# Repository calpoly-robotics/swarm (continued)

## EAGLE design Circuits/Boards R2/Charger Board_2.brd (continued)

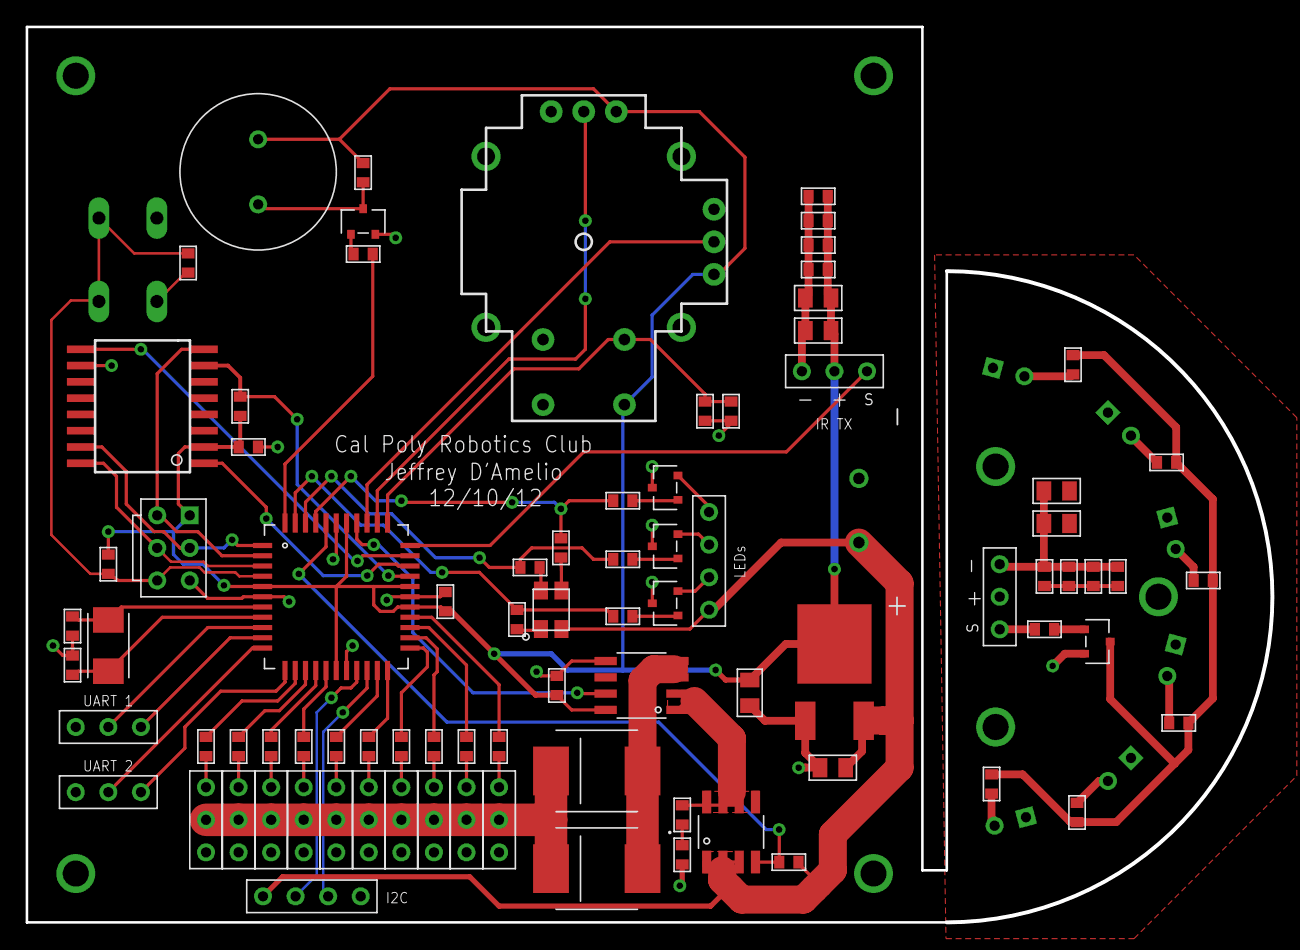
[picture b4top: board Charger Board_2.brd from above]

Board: 2 copper layers, 97.2 x 69.8 mm, 100 parts (1 on the bottom side), 74 nets.

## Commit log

2012-05-16 test
2012-05-16 putting real files in the SVN!
2012-05-16 changed main.c
2012-05-16 added serial library
2012-05-16 minor change
2012-05-17 Cleaned up the serial code a bit.
2012-05-17 renamed uartReady() to uartDataAvailable()
2012-05-17 solid modeled motor and wheels(s)
2012-05-18 uploaded google doc docs
2012-05-22 somebody messed up the svn!
2012-05-23 some ir message code
2012-05-23 ir files
2012-05-23 ir update
2012-05-23 Cleaned up some header files.
2012-05-23 Added parity code.
2012-05-23 better parity
2012-05-23 cleaned up code
2012-05-23 updated a lot of solid modeling parts, not yet complete
2012-05-26 Redid IR stuff to use new struct.
2012-05-26 Added interrupts for transmitting and added start pulse of 3.5 counts to messages.
2012-05-29 Added datasheet.
2012-05-29 Finished Charger?
2012-05-30 updated the wheels, acrylic base, and output a couple images. To laser cut the wheels, it would be best to consider the laser's thickness so that the key is accurate
2012-07-17 massive eagle update
2012-07-18 updates to swarm board circuit
2012-07-19 more work
2012-07-22 added datasheet for mcp73832
2012-07-22 renamed swarm bot overall to swarm board
2012-07-22 added Charger Board.sch
2012-07-22 updated charger schematic, and added swarm board board file
2012-07-22 updated libraries with new datasheets
2012-07-22 Large updates to the charger board
2012-07-24 updates to both boards and libraries. Added hall effect sensors to charger board
2012-08-01 updated libraries and charger board
2012-08-02 updates to both boards
2012-08-02 Started Routing, kill me now
2012-08-11 Finished routing
2012-08-15 changed charge circuit to incorporate mcp73833 and p-fet/diode for ppm
2012-08-16 started routing new charger
2012-08-27 Updated README so it would be more complete.
2012-09-24 basic calculations for the clock in clockCalculations.xlsx
2012-09-24 updated clockCalculations.xlsx to show ticks/second
2012-10-01 updated datasheet
2012-10-01 Updated messages.h to use an enum
2012-10-01 Added test code. Updated main code makefile.
2012-10-01 Added back .c files.
2012-10-01 fixed incorrect vector name
2012-10-01 fixed globals.h
2012-10-05 Instructions for using the laser cutter
2012-10-08 Moved solidworks files into their own folder
2012-10-08 moved more svn stuff
2012-10-13 This code makes the buzzer make noise.
2012-10-14 updated swarm board with R2 and started charger board changes
2012-10-16 Added message format document (and picture).
2012-10-16 fixed syntax
2012-10-16 updated message format
2012-10-17 updated R2 board
2012-10-20 changed spacing on ISP header
2012-10-20 Motors!
2012-10-20 OCR0A, not OCR0B
2012-10-20 reorganizing!
2012-10-20 It drives.
2012-10-20 Added red/green led code
2012-10-20 added u32
2012-10-20 Started work on multitasking
2012-10-20 Clock
2012-10-22 Should work, needs testing.
2012-10-22 Added functions to libraries
2012-10-22 added short range IR code
2012-10-22 We can count on the clock working now.
2012-10-24 modular
2012-10-24 lots of message sending and receiving code
2012-10-24 added tasks
2012-10-24 Merged Jeffrey's task code into the main code folder.
2012-10-24 organized main code
2012-10-25 Clock worked, it's better now too. Don't try to store 32 bit values in 8 bit variables :P
2012-10-25 Clock is more modular now.
2012-11-05 This is a test
2012-11-05 testing svn
2012-11-16 saving charger changes
2012-11-17 combined drivers
2012-11-26 completed schematic for the charger board
2012-11-26 more board updates
2012-11-26 added sparkfun drc
2012-11-27 started adding rgb edge lighting hardware
2012-12-03 fixed led on swarm board
2012-12-09 added boms for run 2
2012-12-09 slight updates to part values to account for availibility
2012-12-10 added gerbers for production
2013-02-15 reorganized code, added some new base code
2013-10-14 Removed drivers folder
2013-10-14 Removed files
2013-10-14 Reorganized
2013-10-14 Reorganized. Conversion from svn is complete. I think.
2013-11-01 Added base files
2013-11-01 Removed binary files
2013-11-02 Added .gitignore
2013-11-02 Clock init stuff
2013-11-02 Added basic code for the motors. Need to figure out what the pins mean...
2013-11-02 Minor work on motor init
2013-11-03 On branch master Changes to be committed: (use "git reset HEAD <file>..." to unstage)
    modified: Robot/Makefile
    modified: Robot/main.c
    modified: Robot/main.elf
    modified: Robot/main.hex
    modified: Robot/swarm.conf
2013-11-14 Added a bunch of drivers
2013-11-15 Did some serial stuff
2013-11-15 More work done on serial
2013-11-16 did some stuff...
2013-11-16 Should now be able to add tasks with an expanding array
2013-11-16 I think tasks work now...
2013-11-16 Well, tasks should be done...
2013-11-16 added dummy tasks for all the things
2013-11-16 Added all dummy tasks and MULTITASKING WORKS!!!
2013-11-16 Code mostly done for IR. Just need recieve manager...
2013-11-16 IR is done. I think.. Need to test.
2013-11-16 Renamed some stuff.
2013-11-16 Added header for TWI(I2C)
2013-11-16 Added eeprom and twi(i2c) templates
2013-11-16 Working on TWI(I2C) protocol...
2013-11-17 More work on TWI
2013-11-17 Stuff...
2013-11-17 Filled out README.md with more notes
2013-11-17 Much work done on TWI
2013-11-18 changed header defs slightly. can read eeprom log
2013-11-18 More improvements on eeprom stuff. i think it's "done"
2013-11-18 i think transmittion is done
2013-11-18 Added gitignore
2013-11-18 Auto retransmit of messages and ignore our messages that got retransmitted
2013-11-18 Working on pins.h
2013-11-18 I think pins.h is done?
2013-11-18 Fixed a typo and wrote down some todos
2013-11-19 Part of buzzer code done. The annoying math part
2013-11-19 Added some buzzer stuff
2013-11-19 Too hard to test without actual hardware...:
2013-11-21 stuff
2013-11-23 Led stuff done. I think
2013-12-12 Began work on battery monitoring task. Fixed adc code. SERIAL!!!
2013-12-12 Add base code
2013-12-12 Minor changes to main and battery
2013-12-12 warning level mostly done
2013-12-13 Low power modes done coding. Testing to ensue
2013-12-13 Fixed possible uart buffer problems
2013-12-13 Minor changes to serial
2013-12-13 Goofed with the merge
2013-12-13 main now echos anything sent
2014-01-26 such change.
2014-01-30 Added some shit right there. Yup
2014-01-31 updated project file
2014-01-31 fixed project file
2014-01-31 Updated the uart code
2014-02-01 fixed some multitasking stuff
2014-02-02 much pain...
2014-02-02 Forgot these files
2014-02-07 IR is closer to working....
2014-02-07 asdf
2014-02-27 Working on ir test
2014-03-01 There are some shenanigans going on with the IR recieve code... Debuging pointer bullshit.
2014-03-01 IR interrupts are working with proper timing. Messages aren't quite working...
2014-03-02 IR is funky, but prints WORK REALLY WELL
2014-03-02 Better serial. IR ALMOST working.
2014-03-02 IR WORKS MOTHAFUCKA
2014-03-02 Send sequence working. checksum and everything working. cool beans.
2014-03-02 Going to add direction and time to the message
2014-03-03 Send sequence works. Old messages get rejected
2014-03-04 Working on multi direction
2014-03-05 direction not working properly...
2014-03-05 Controller resets whenever we try to read from PCMSK2
2014-03-06 Changed .gitignore
2014-03-06 More changesy
2014-03-06 Removed the sublime workspace file
2014-03-06 Git is being finicky...
2014-03-10 adding r3 to main forky thing
2014-03-13 updated r3 to match my branch
    This is now the ONLY accurate branch
2014-03-13 more
2014-03-13 more stuff dimensions and things
2014-03-14 fixed derp
2014-03-14 added up to date solid models
2014-03-14 charger cad
2014-03-14 Charger slit spacing fixed
    1in to .9in center to center of outside slits
2014-03-15 updated charger board stuff
2014-03-15 "Fixed" multitasking
2014-03-15 Working on code.
2014-03-15 MORE STUFF
    LEDS, TX/RX, WHATEVER
2014-03-16 Both boards almost ready for routing
2014-03-16 same as last
2014-03-16 picked new 3v regulator
2014-03-17 ready to route
2014-03-17 more routing
2014-03-17 almost there
2014-03-17 schematic at 100%
2014-03-17 swarm board routing done!
2014-03-17 something
2014-03-17 Started charger board
    Saved as separate file so I don't mess anything important up
2014-03-20 both boards are routed
2014-03-20 changed programming header label
2014-03-21 adjusted silkscreen and added power switch
2014-03-21 updated part outlines in tplace layer
2014-03-21 believe boards are complete including silkscreen
2014-03-21 Created BOMS
2014-03-21 Gerbers generated and zipped for boards and stencils
2014-03-21 Added BOMs after they got deleted somehow -.-
2014-03-21 BOMS and boards updated with a few slight value changes to reflect component availability
2014-03-24 Modified Swarm board to sensor board connection to meet seeed requirements
2014-03-29 Made similar panelization modification to charger board
2014-04-22 add ir tabs and led holder
